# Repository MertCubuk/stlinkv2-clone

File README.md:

# ST-Link V2 Clone (Rev.2) — KiCad PCB Design

STM32 tabanlı bir ST-Link V2 programlayıcı kart tasarımıdır.  
Projede amaç, USB–SWD arayüzünü stabilize edecek şekilde hat eşitlemesi yapılmış,  
üretime uygun iki katmanlı bir PCB ortaya çıkarmaktır.

---

## Teknik Özellikler

- Mikrodenetleyici: STM32F103C8T6  
- Bağlantı: USB FS (12 Mbps), D+ / D− diferansiyel hat eş uzunluklu  
- Besleme: 5V → 3.3V LDO regülatör  
- Koruma: TVS diyot ile ESD koruması
- Arabirim: SWD, UART pin header (JTAG alternatifi)  
- Katman sayısı: 2  
- Minimum iz kalınlığı: 0.25 mm  
- Minimum via boyutu: 0.3 / 0.6 mm  
- PCB boyutu: Yaklaşık 70.75 × 30 mm  
- DRC: Hatasız (clearance & unconnected 0)

---

## Tasarım Notları

- D+ / D− hatları eş uzunlukta ve paralel olarak route edildi.  
- 3.3V ve 5V güç yolları kalınlaştırılarak düşük dirençli hat elde edildi.  
- Decoupling kondansatörleri MCU’ya fiziksel olarak en yakın konumda yerleştirildi.  
- Kristal çevresi kısa loop ve GND guard ile izole edildi.  
- GND plane sürekliliği korunarak düşük EMI hedeflendi.  
- Bileşenlerin silkscreen konumları okunabilirlik ve üretim kolaylığına göre düzenlendi.

---

## Görseller

### PCB Üst Katman (3D)

### PCB Alt Katman (3D)

### Düzenleme Görünümü (KiCad)

---

## Üretim ve Çıktılar

- Gerber + Drill dosyaları `outputs/gerbers_drill.rar` klasöründe yer alır.  
- JLCPCB / PCBWay üretim kurallarına uyumludur.  
- Şematik dosyası `.pdf` formatında eklendi (`stlinkv2_schmatic.pdf`).  
- BOM listesi ve netlist, KiCad v9+ üzerinde otomatik oluşturulabilir.

---

## Tasarım

Mert Çubuk  
Elektrik-Elektronik Mühendisi | Embedded Systems & PCB Design  
Ekim 2025  
LinkedIn: [https://www.linkedin.com/in/mert-%C3%A7ubuk-06b53536a/]

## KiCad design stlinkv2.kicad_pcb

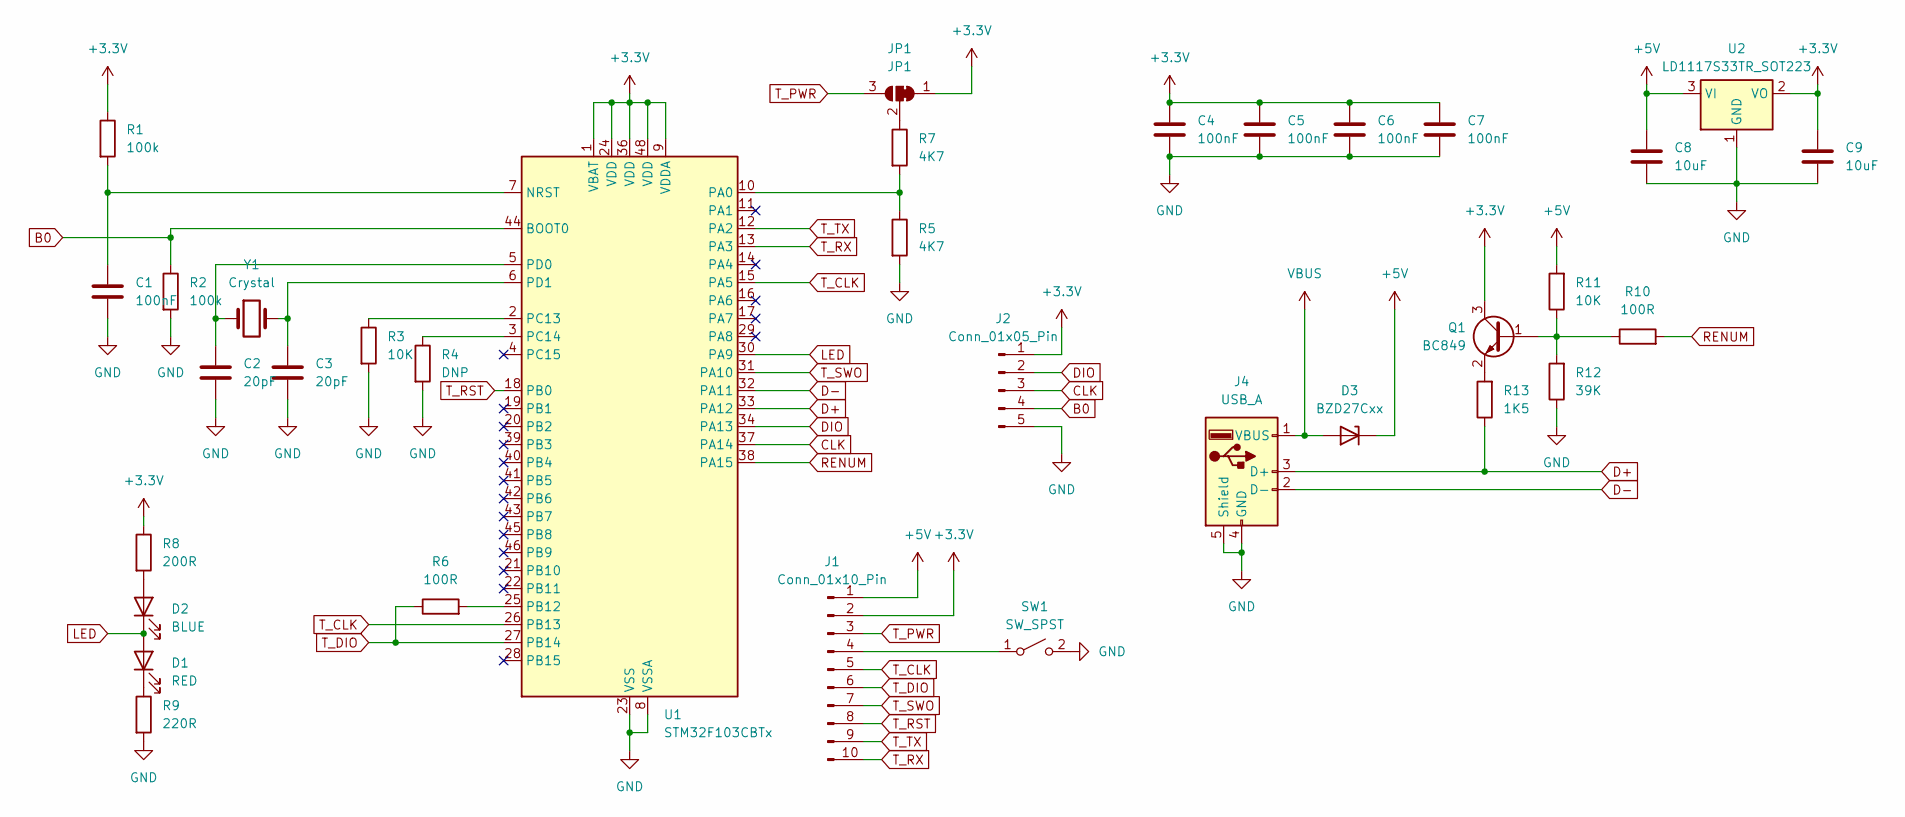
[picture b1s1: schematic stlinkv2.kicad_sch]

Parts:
C1, C4, C5, C6, C7: 100nF; C_0603_1608Metric
C2, C3: 20pF; C_0603_1608Metric
C8, C9: 10uF; C_0603_1608Metric
D1: RED; LED_0603_1608Metric
D2: BLUE; LED_0603_1608Metric
D3: BZD27Cxx; D_SMF
J1: Conn_01x10_Pin; PinSocket_1x10_P2.54mm_Vertical
J2: Conn_01x05_Pin; PinSocket_1x05_P2.54mm_Vertical
J4: USB_A; USB_A_Molex_105057_Vertical
JP1: JP1; SolderJumper-3_P1.3mm_Bridged12_Pad1.0x1.5mm
Q1: BC849; SOT-23
R1, R2: 100k; R_0603_1608Metric
R3, R11: 10K; R_0603_1608Metric
R4: DNP; R_0603_1608Metric
R5, R7: 4K7; R_0603_1608Metric
R6, R10: 100R; R_0603_1608Metric
R8: 200R; R_0603_1608Metric
R9: 220R; R_0603_1608Metric
R12: 39K; R_0603_1608Metric
R13: 1K5; R_0603_1608Metric
SW1: SW_SPST; SW_DIP_SPSTx01_Slide_6.7x4.1mm_W7.62mm_P2.54mm_LowProfile
U1: STM32F103CBTx; LQFP-48_7x7mm_P0.5mm
U2: LD1117S33TR_SOT223; SOT-223-3_TabPin2
Y1: Crystal; Crystal_SMD_ECS_CSM3X-2Pin_7.6x4.1mm

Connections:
+3.3V: C4.2, C5.2, C6.2, C7.2, C9.2, J1.2, J2.1, JP1.1 (A), Q1.3 (C), R1.1, R8.1, U1.1 (VBAT), U1.9 (VDDA), U1.24 (VDD), U1.36 (VDD), U1.48 (VDD), U2.2 (VO)
+5V: C8.2, D3.1 (K), J1.1, R11.2, U2.3 (VI)
B0: J2.4, R2.1, U1.44 (BOOT0)
CLK: J2.3, U1.37 (PA14)
D+: J4.3 (D+), R13.1, U1.33 (PA12)
D-: J4.2 (D-), U1.32 (PA11)
DIO: J2.2, U1.34 (PA13)
GND: C1.2, C2.2, C3.2, C4.1, C5.1, C6.1, C7.1, C8.1, C9.1, J2.5, J4.4 (GND), J4.5 (Shield), R2.2, R3.2, R4.2, R5.2, R9.2, R12.1, SW1.2 (B), U1.8 (VSSA), U1.23 (VSS), U1.35 (VSS), U1.47 (VSS), U2.1 (GND)
LED: D1.2 (A), D2.1 (K), U1.30 (PA9)
unnamed: D1.1 (K), R9.1
unnamed: D2.2 (A), R8.2
unnamed: J1.4, SW1.1 (A)
unnamed: JP1.2 (C), R7.1
unnamed: Q1.1 (B), R10.1, R11.1, R12.2
unnamed: Q1.2 (E), R13.2
unnamed: C1.1, R1.2, U1.7 (NRST)
unnamed: R5.1, R7.2, U1.10 (PA0)
unnamed: R6.2, U1.25 (PB12)
unnamed: R3.1, U1.2 (PC13)
unnamed: R4.1, U1.3 (PC14)
unnamed: C2.1, U1.5 (PD0), Y1.1
unnamed: C3.1, U1.6 (PD1), Y1.2
RENUM: R10.2, U1.38 (PA15)
T_CLK: J1.5, U1.15 (PA5), U1.26 (PB13)
T_DIO: J1.6, R6.1, U1.27 (PB14)
T_PWR: J1.3, JP1.3 (B)
T_RST: J1.8, U1.18 (PB0)
T_RX: J1.10, U1.13 (PA3)
T_SWO: J1.7, U1.31 (PA10)
T_TX: J1.9, U1.12 (PA2)
VBUS: D3.2 (A), J4.1 (VBUS)

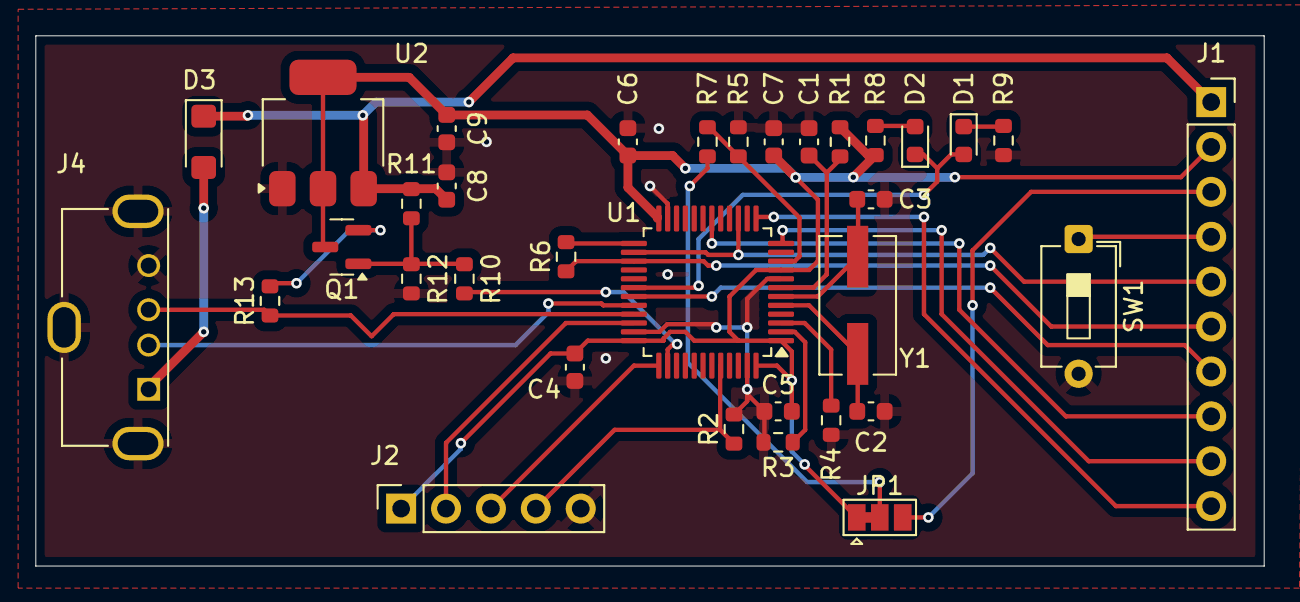
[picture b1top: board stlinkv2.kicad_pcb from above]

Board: 2 copper layers, 69.5 x 30.0 mm, 34 parts (0 on the bottom side), 31 nets.

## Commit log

2025-10-23 Initial commit - ST-Link V2 Clone Rev2
2025-10-23 Add README.
2025-10-23 README update.
